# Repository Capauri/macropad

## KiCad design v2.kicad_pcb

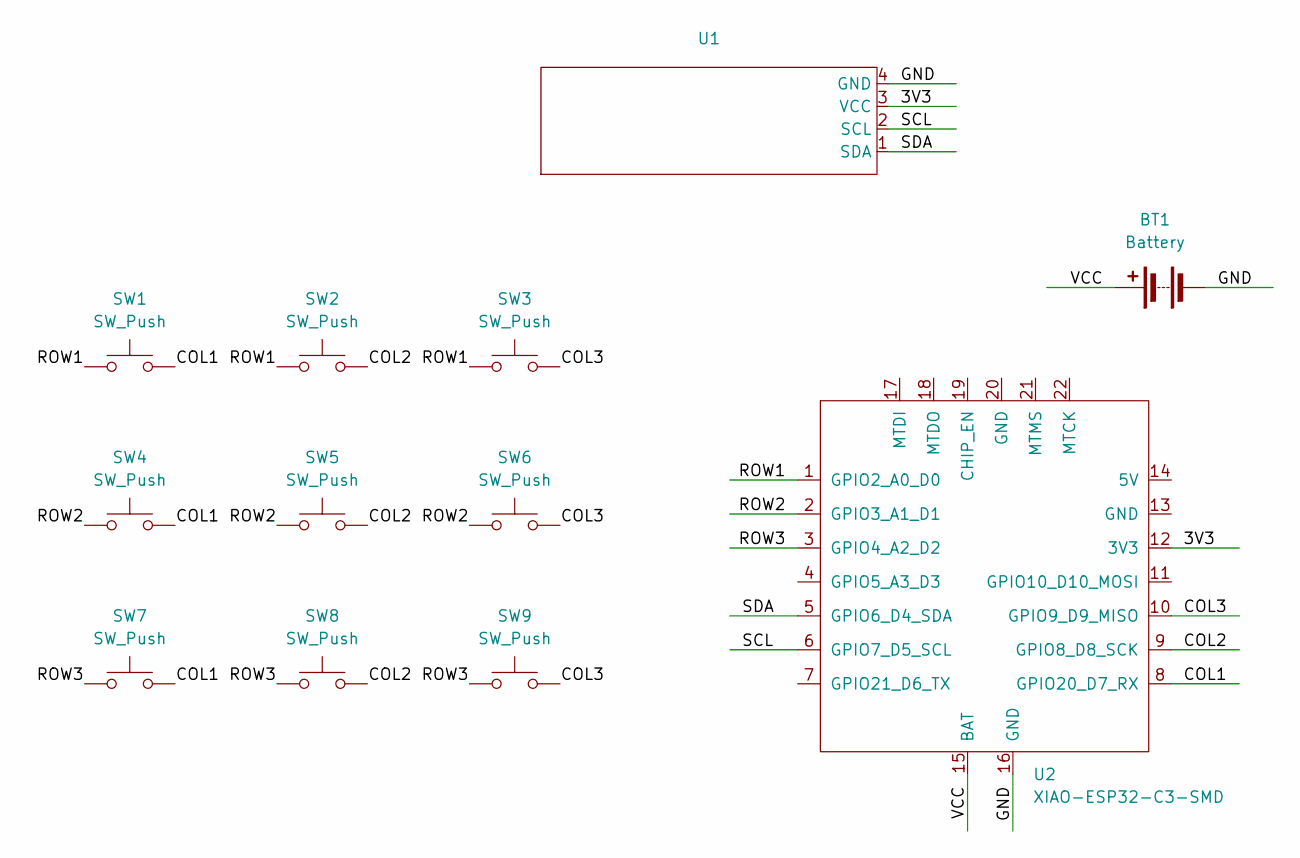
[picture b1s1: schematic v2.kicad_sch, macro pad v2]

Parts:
BT1: Battery; JST_GH_SM02B-GHS-TB_1x02-1MP_P1.25mm_Horizontal
SW1, SW2, SW3, SW4, SW5, SW6, SW7, SW8, SW9: SW_Push; Kailh_socket_MX
U1: 0.91 OLED 128x32
U2: XIAO-ESP32-C3-SMD; XIAO-ESP32C3-SMD

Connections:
/3V3: U1.3 (VCC), U2.12 (3V3)
/COL1: SW1.2, SW4.2, SW7.2, U2.8 (GPIO20_D7_RX)
/COL2: SW2.2, SW5.2, SW8.2, U2.9 (GPIO8_D8_SCK)
/COL3: SW3.2, SW6.2, SW9.2, U2.10 (GPIO9_D9_MISO)
/GND: BT1.2 (-), U1.4 (GND), U2.16 (GND)
/ROW1: SW1.1, SW2.1, SW3.1, U2.1 (GPIO2_A0_D0)
/ROW2: SW4.1, SW5.1, SW6.1, U2.2 (GPIO3_A1_D1)
/ROW3: SW7.1, SW8.1, SW9.1, U2.3 (GPIO4_A2_D2)
/SCL: U1.2 (SCL), U2.6 (GPIO7_D5_SCL)
/SDA: U1.1 (SDA), U2.5 (GPIO6_D4_SDA)
/VCC: BT1.1 (+), U2.15 (BAT)

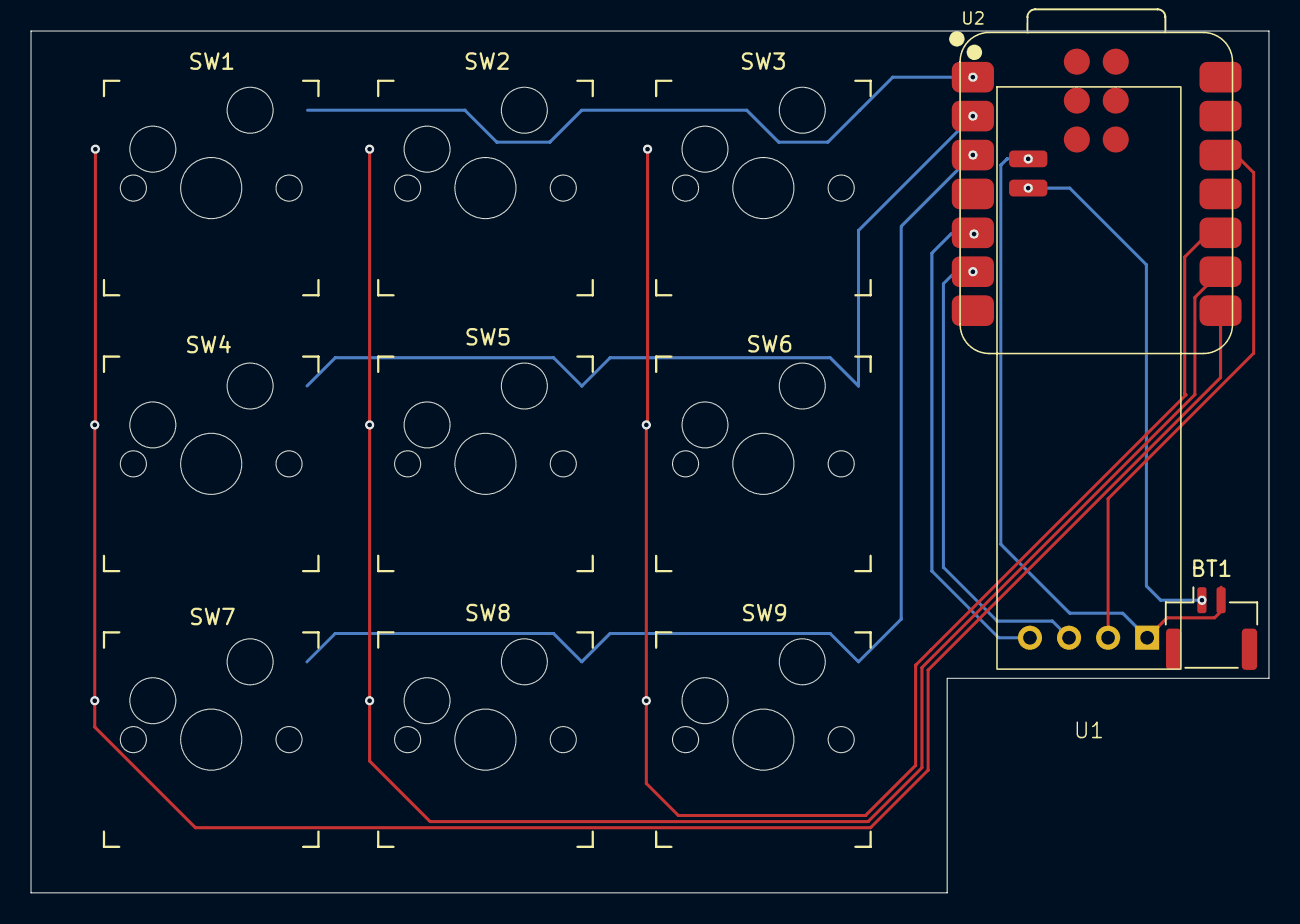
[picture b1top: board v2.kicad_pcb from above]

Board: 2 copper layers, 80.8 x 56.2 mm, 12 parts (0 on the bottom side), 11 nets.

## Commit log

2025-05-19 init
